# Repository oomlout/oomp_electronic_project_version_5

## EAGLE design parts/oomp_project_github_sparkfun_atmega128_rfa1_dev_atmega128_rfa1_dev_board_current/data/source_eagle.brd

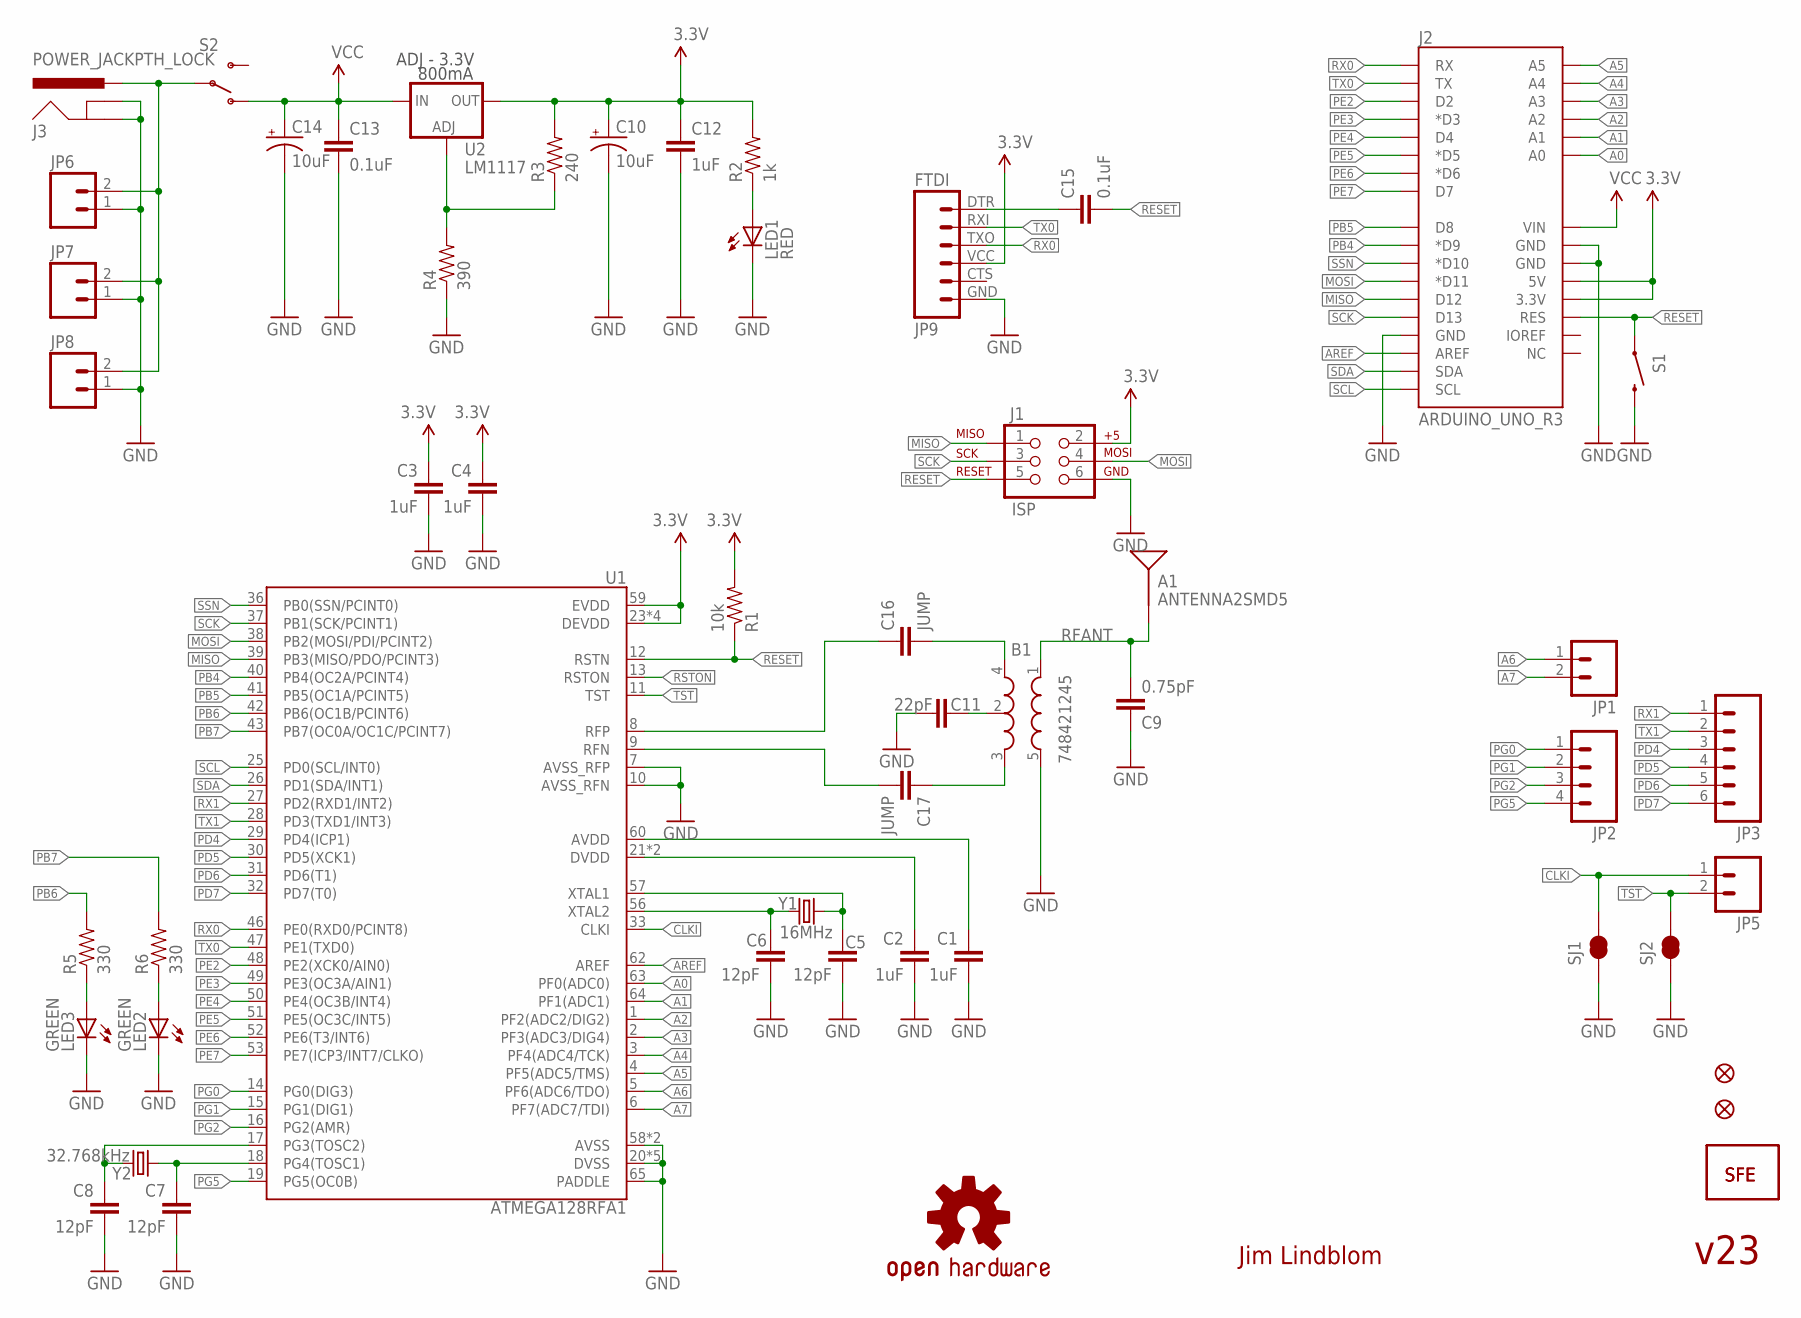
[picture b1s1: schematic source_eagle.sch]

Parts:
A1: ANTENNA2SMD5; ANTENNA-CHIP5
B1: 748421245; BALUN
C1, C2, C3, C4, C12: 1uF; 0402-CAP
C5, C6, C7, C8: 12pF; 0402-CAP
C9: 0.75pF; 0402-CAP
C10, C14: 10uF; EIA3216
C11: 22pF; 0402-CAP
C13, C15: 0.1uF; 0402-CAP
C16, C17: JUMP; 0402-CAP
FID1, FID2: FIDUCIALUFIDUCIAL; MICRO-FIDUCIAL
J1: ISP; 2X3-NS
J2: ARDUINO_UNO_R3
J3: POWER_JACKPTH_LOCK; POWER_JACK_PTH_LOCK
JP1, JP5, JP7: M021X02_NO_SILK; 1X02_NO_SILK
JP2: M041X04_NO_SILK; 1X04_NO_SILK
JP3: M06SIP-NS; 1X06_NS
JP4, JP10: LOGO-SFENEW; SFE-NEW-WEBLOGO
JP6: M02JST-PTH-2; JST-2-PTH
JP8: M023.5MM-NO_SILK; SCREWTERMINAL-3.5MM-2-NS
JP9: FTDI; FTDI_BASIC
LED1: RED; LED-0603
LED2, LED3: GREEN; LED-0603
R1: 10k; 0402-RES
R2: 1k; 0402-RES
R3: 240; 0402-RES
R4: 390; 0402-RES
R5, R6: 330; 0402-RES
S1: SWITCH-MOMENTARY-2SMD; TACTILE_SWITCH_SMD
S2: SWITCH-SPST-SMD-A
SJ1, SJ2: SOLDERJUMPERTRACE; SJ_2S-TRACE
U1: ATMEGA128RFA1; QFN-64
U2: LM1117; SOT223
U$1: OSHW-LOGOS; OSHW-LOGO-S
Y1: 16MHz; CRYSTAL-SMD-5X3
Y2: 32.768kHz; CRYSTAL-32KHZ-SMD

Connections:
3.3V: C3.1, C4.1, C10.A (+), C12.1, J1.2, J2.3.3V, J2.5V, JP9.VCC (4), R1.2, R2.2, R3.2, U1.23 (DEVDD), U1.34 (DEVDD), U1.44 (DEVDD), U1.54 (DEVDD), U1.59 (EVDD), U2.2 (OUT)
A0: J2.A0, U1.63 (PF0(ADC0))
A1: J2.A1, U1.64 (PF1(ADC1))
A2: J2.A2, U1.1 (PF2(ADC2/DIG2))
A3: J2.A3, U1.2 (PF3(ADC3/DIG4))
A4: J2.A4, U1.3 (PF4(ADC4/TCK))
A5: J2.A5, U1.4 (PF5(ADC5/TMS))
A6: JP1.1, U1.5 (PF6(ADC6/TDO))
A7: JP1.2, U1.6 (PF7(ADC7/TDI))
AREF: J2.AREF, U1.62 (AREF)
AVDD: C1.1, U1.60 (AVDD)
CLKI: JP5.1, SJ1.2, U1.33 (CLKI)
DTR: C15.1, JP9.DTR (1)
DVDD: C2.1, U1.21 (DVDD), U1.22 (DVDD)
FB: R3.1, R4.2, U2.1 (ADJ)
GND: B1.5 (GND), C1.2, C2.2, C3.2, C4.2, C5.2, C6.2, C7.2, C8.2, C9.1, C10.C (-), C11.2, C12.2, C13.2, C14.C (-), J1.6, J2.GND@0 (GND), J2.GND@1 (GND), J2.GND@2 (GND), J3.GND, J3.GNDBREAK, JP6.1, JP7.1, JP8.1, JP9.GND (6), LED1.C, LED2.C, LED3.C, R4.1, S1.3 (2), SJ1.1, SJ2.1, U1.7 (AVSS_RFP), U1.10 (AVSS_RFN), U1.20 (DVSS), U1.24 (DVSS), U1.35 (DVSS), U1.45 (DVSS), U1.55 (DVSS), U1.58 (AVSS), U1.61 (AVSS), U1.65 (PADDLE)
MISO: J1.1, J2.D12, U1.39 (PB3(MISO/PDO/PCINT3))
MOSI: J1.4, J2.D11 (*D11), U1.38 (PB2(MOSI/PDI/PCINT2))
unnamed: LED1.A, R2.1
unnamed: C5.1, U1.57 (XTAL1), Y1.3 (2)
unnamed: C6.1, U1.56 (XTAL2), Y1.1
unnamed: C7.1, U1.18 (PG4(TOSC1)), Y2.X1 (1)
unnamed: C8.1, U1.17 (PG3(TOSC2)), Y2.X2 (2)
unnamed: B1.2 (GND), C11.1
unnamed: LED3.A, R5.1
unnamed: J3.PWR, JP6.2, JP7.2, JP8.2, S2.2
unnamed: B1.4 (OUT1), C16.2
unnamed: B1.3 (OUT2), C17.1
unnamed: LED2.A, R6.1
PB4: J2.D9 (*D9), U1.40 (PB4(OC2A/PCINT4))
PB5: J2.D8, U1.41 (PB5(OC1A/PCINT5))
PB6: R5.2, U1.42 (PB6(OC1B/PCINT6))
PB7: R6.2, U1.43 (PB7(OC0A/OC1C/PCINT7))
PD4: JP3.3, U1.29 (PD4(ICP1))
PD5: JP3.4, U1.30 (PD5(XCK1))
PD6: JP3.5, U1.31 (PD6(T1))
PD7: JP3.6, U1.32 (PD7(T0))
PE2: J2.D2, U1.48 (PE2(XCK0/AIN0))
PE3: J2.D3 (*D3), U1.49 (PE3(OC3A/AIN1))
PE4: J2.D4, U1.50 (PE4(OC3B/INT4))
PE5: J2.D5 (*D5), U1.51 (PE5(OC3C/INT5))
PE6: J2.D6 (*D6), U1.52 (PE6(T3/INT6))
PE7: J2.D7, U1.53 (PE7(ICP3/INT7/CLKO))
PG0: JP2.1, U1.14 (PG0(DIG3))
PG1: JP2.2, U1.15 (PG1(DIG1))
PG2: JP2.3, U1.16 (PG2(AMR))
PG5: JP2.4, U1.19 (PG5(OC0B))
RESET: C15.2, J1.5, J2.RES, R1.1, S1.1, U1.12 (RSTN)
RFANT: A1.FEED, B1.1 (IN), C9.2
RFN: C17.2, U1.9 (RFN)
RFP: C16.1, U1.8 (RFP)
RSTON: U1.13 (RSTON)
RX0: J2.RX, JP9.TXO (3), U1.46 (PE0(RXD0/PCINT8))
RX1: JP3.1, U1.27 (PD2(RXD1/INT2))
SCK: J1.3, J2.D13, U1.37 (PB1(SCK/PCINT1))
SCL: J2.SCL, U1.25 (PD0(SCL/INT0))
SDA: J2.SDA, U1.26 (PD1(SDA/INT1))
SSN: J2.D10 (*D10), U1.36 (PB0(SSN/PCINT0))
TST: JP5.2, SJ2.2, U1.11 (TST)
TX0: J2.TX, JP9.RXI (2), U1.47 (PE1(TXD0))
TX1: JP3.2, U1.28 (PD3(TXD1/INT3))
VCC: C13.1, C14.A (+), J2.VIN, S2.1 (O), U2.3 (IN)

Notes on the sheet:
Jim Lindblom
800mA
ADJ - 3.3V
v23

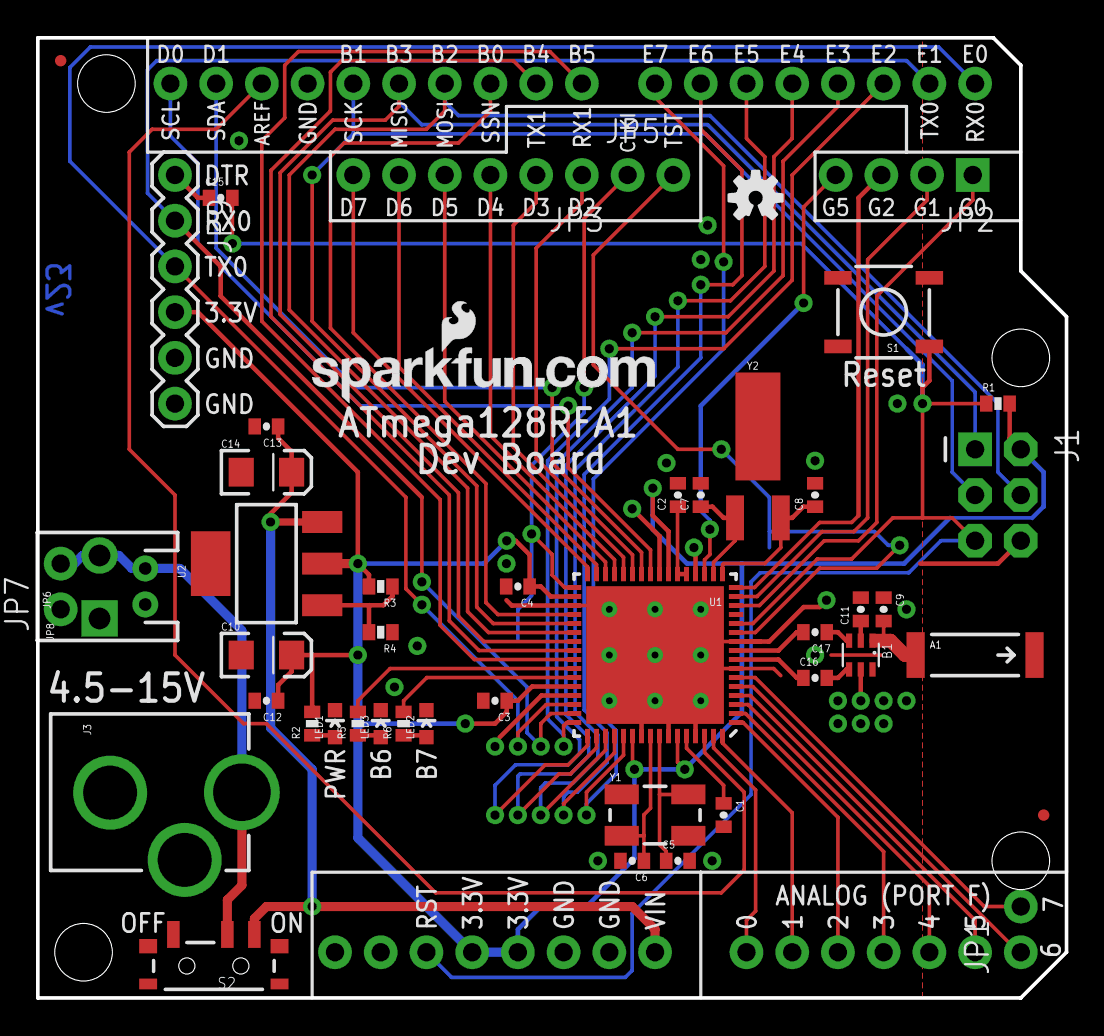
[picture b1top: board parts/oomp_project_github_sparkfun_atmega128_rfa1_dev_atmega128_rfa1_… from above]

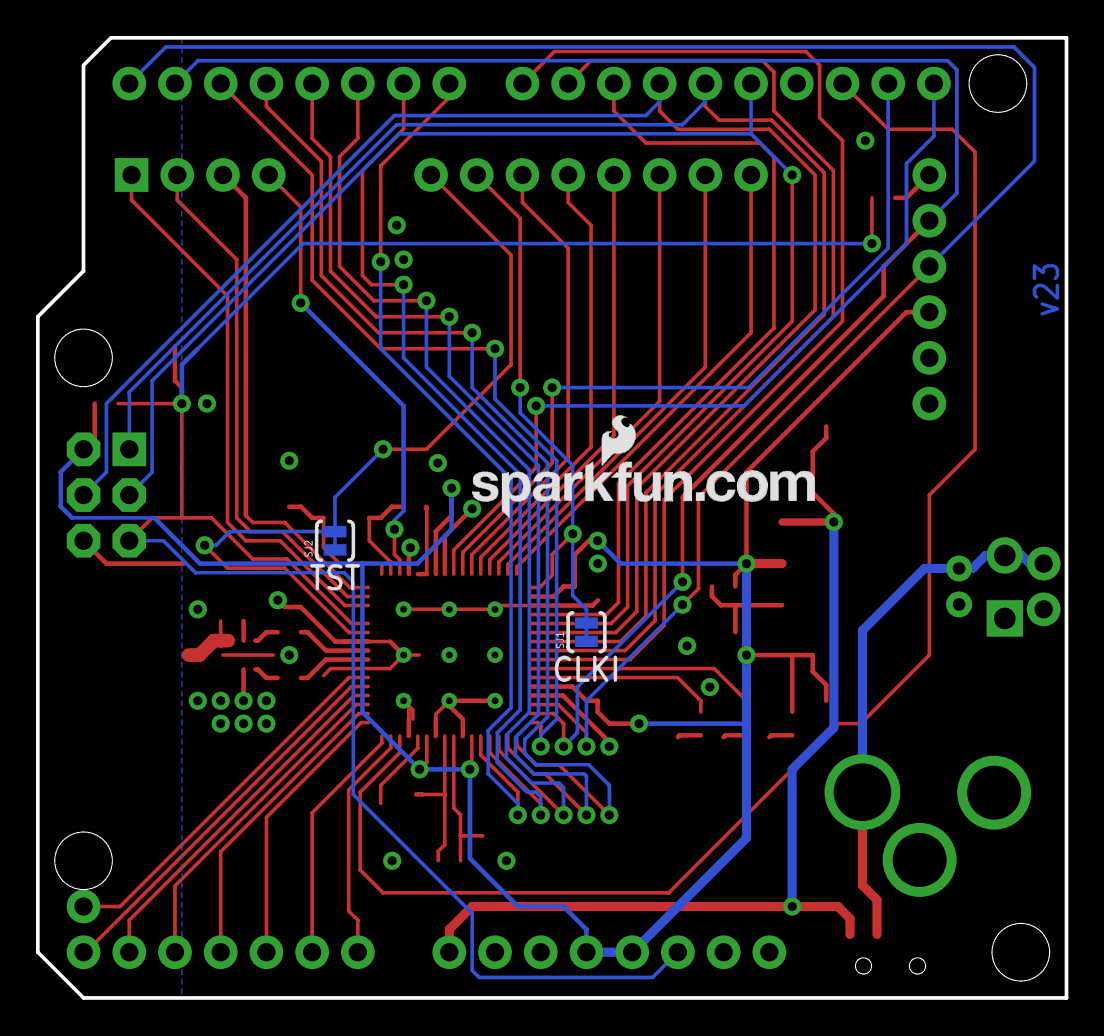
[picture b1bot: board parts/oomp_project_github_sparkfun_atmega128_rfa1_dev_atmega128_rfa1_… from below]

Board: 2 copper layers, 57.1 x 53.3 mm, 52 parts (3 on the bottom side), 61 nets.

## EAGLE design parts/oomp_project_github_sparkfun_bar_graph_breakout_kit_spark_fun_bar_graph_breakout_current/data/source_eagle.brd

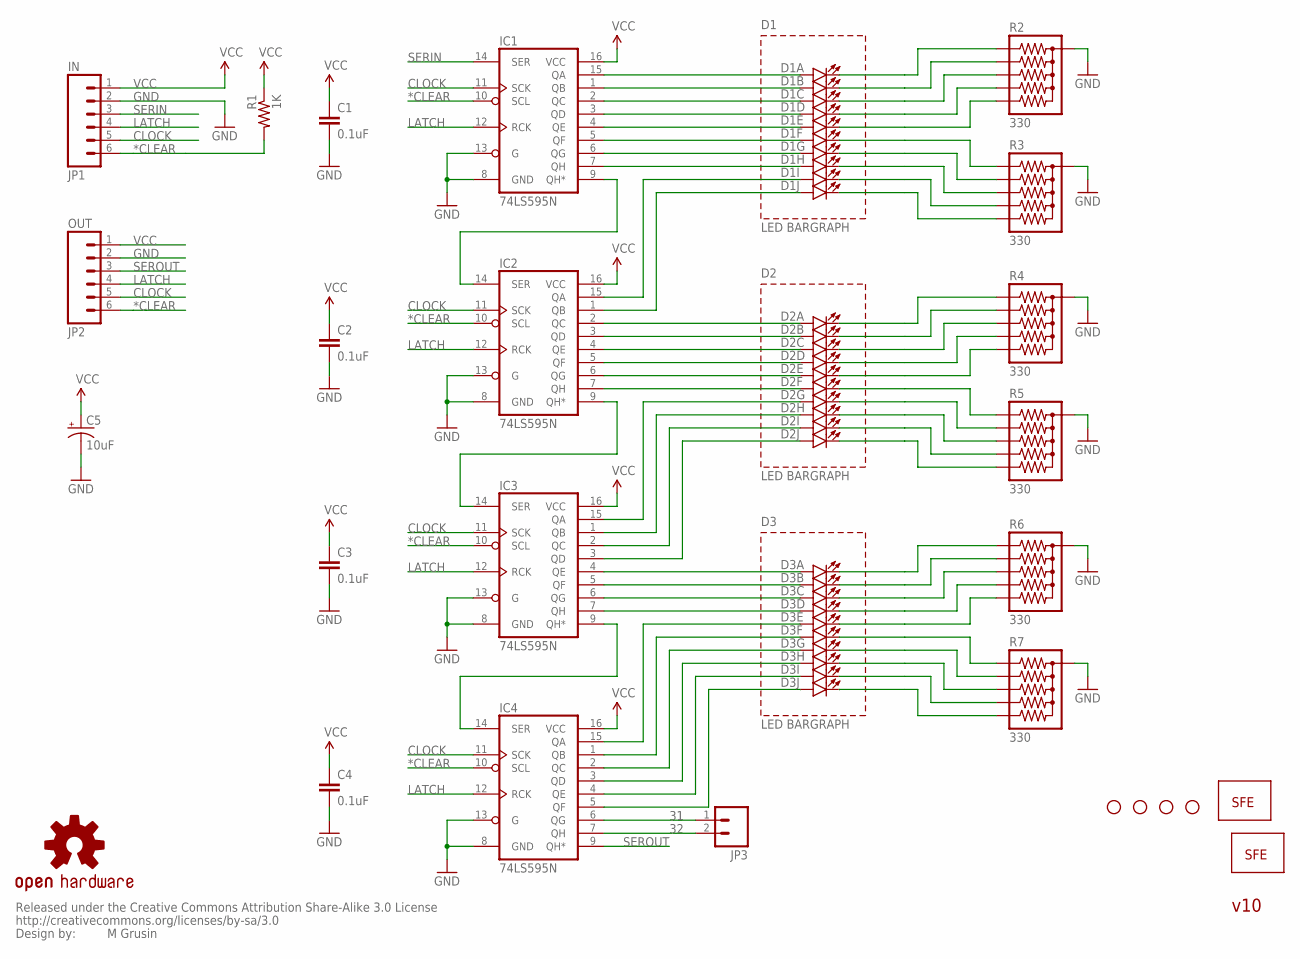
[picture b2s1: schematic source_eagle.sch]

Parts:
C1, C2, C3, C4: 0.1uF; CAP-PTH-SMALL2
C5: 10uF; CPOL-RADIAL-10UF-25V
D1, D2, D3: LED_BARGRAPH_10; LED_BARGAPH_10
IC1, IC2, IC3, IC4: 74LS595N; DIL16
JP1: IN; 1X06
JP2: OUT; 1X06
JP3: M02PTH; 1X02
LOGO1: LOGO-SFENW2; SFE-NEW-WEB
LOGO2: LOGO-SFESK; SFE-LOGO-FLAME
R1: 1K; AXIAL-0.3
R2, R3, R4, R5, R6, R7: 330; RPACK-SIP-PTH-5
SO1, SO2, SO3, SO4: STAND-OFF
U$5: OSHW-LOGOM; OSHW-LOGO-M
U$6: CREATIVE_COMMONS

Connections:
31: IC4.6 (QG), JP3.1
32: IC4.7 (QH), JP3.2
*CLEAR: IC1.10 (SCL), IC2.10 (SCL), IC3.10 (SCL), IC4.10 (SCL), JP1.6, JP2.6, R1.P$2 (2)
CLOCK: IC1.11 (SCK), IC2.11 (SCK), IC3.11 (SCK), IC4.11 (SCK), JP1.5, JP2.5
GND: C1.2, C2.2, C3.2, C4.2, C5.2 (-), IC1.8 (GND), IC1.13 (G), IC2.8 (GND), IC2.13 (G), IC3.8 (GND), IC3.13 (G), IC4.8 (GND), IC4.13 (G), JP1.2, JP2.2, R2.P$1 (1), R3.P$1 (1), R4.P$1 (1), R5.P$1 (1), R6.P$1 (1), R7.P$1 (1)
LATCH: IC1.12 (RCK), IC2.12 (RCK), IC3.12 (RCK), IC4.12 (RCK), JP1.4, JP2.4
unnamed: D1.1 (A), IC1.15 (QA)
unnamed: D1.2 (A), IC1.1 (QB)
unnamed: D1.3 (A), IC1.2 (QC)
unnamed: D1.4 (A), IC1.3 (QD)
unnamed: D1.5 (A), IC1.4 (QE)
unnamed: D1.6 (A), IC1.5 (QF)
unnamed: D1.7 (A), IC1.6 (QG)
unnamed: D1.8 (A), IC1.7 (QH)
unnamed: D1.9 (A), IC2.15 (QA)
unnamed: D1.10 (A), IC2.1 (QB)
unnamed: D2.8 (A), IC3.1 (QB)
unnamed: D2.7 (A), IC3.15 (QA)
unnamed: D2.9 (A), IC3.2 (QC)
unnamed: D2.10 (A), IC3.3 (QD)
unnamed: D3.1 (A), IC3.4 (QE)
unnamed: D3.2 (A), IC3.5 (QF)
unnamed: D3.3 (A), IC3.6 (QG)
unnamed: D3.4 (A), IC3.7 (QH)
unnamed: D2.1 (A), IC2.2 (QC)
unnamed: D2.2 (A), IC2.3 (QD)
unnamed: D2.3 (A), IC2.4 (QE)
unnamed: D2.4 (A), IC2.5 (QF)
unnamed: D2.5 (A), IC2.6 (QG)
unnamed: D2.6 (A), IC2.7 (QH)
unnamed: D1.20 (C), R2.P$2 (2)
unnamed: D1.19 (C), R2.P$3 (3)
unnamed: D3.5 (A), IC4.15 (QA)
unnamed: D3.6 (A), IC4.1 (QB)
unnamed: D1.18 (C), R2.P$4 (4)
unnamed: D1.17 (C), R2.P$5 (5)
unnamed: D1.16 (C), R2.P$6 (6)
unnamed: D1.15 (C), R3.P$2 (2)
unnamed: D1.14 (C), R3.P$3 (3)
unnamed: D1.13 (C), R3.P$4 (4)
unnamed: D1.12 (C), R3.P$5 (5)
unnamed: D1.11 (C), R3.P$6 (6)
unnamed: D2.20 (C), R4.P$2 (2)
unnamed: D2.19 (C), R4.P$3 (3)
unnamed: D3.7 (A), IC4.2 (QC)
unnamed: D3.8 (A), IC4.3 (QD)
unnamed: D3.9 (A), IC4.4 (QE)
unnamed: D3.10 (A), IC4.5 (QF)
unnamed: D2.18 (C), R4.P$4 (4)
unnamed: D2.17 (C), R4.P$5 (5)
unnamed: D2.16 (C), R4.P$6 (6)
unnamed: D2.15 (C), R5.P$2 (2)
unnamed: D2.14 (C), R5.P$3 (3)
unnamed: D2.13 (C), R5.P$4 (4)
unnamed: D2.12 (C), R5.P$5 (5)
unnamed: D2.11 (C), R5.P$6 (6)
unnamed: D3.20 (C), R6.P$2 (2)
unnamed: D3.19 (C), R6.P$3 (3)
unnamed: D3.18 (C), R6.P$4 (4)
unnamed: D3.17 (C), R6.P$5 (5)
unnamed: D3.16 (C), R6.P$6 (6)
unnamed: D3.15 (C), R7.P$2 (2)
unnamed: D3.14 (C), R7.P$3 (3)
unnamed: D3.13 (C), R7.P$4 (4)
unnamed: D3.12 (C), R7.P$5 (5)
unnamed: D3.11 (C), R7.P$6 (6)
unnamed: IC1.9 (QH*), IC2.14 (SER)
unnamed: IC2.9 (QH*), IC3.14 (SER)
unnamed: IC3.9 (QH*), IC4.14 (SER)
SERIN: IC1.14 (SER), JP1.3
SEROUT: IC4.9 (QH*), JP2.3
VCC: C1.1, C2.1, C3.1, C4.1, C5.1 (+), IC1.16 (VCC), IC2.16 (VCC), IC3.16 (VCC), IC4.16 (VCC), JP1.1, JP2.1, R1.P$1 (1)

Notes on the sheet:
M Grusin
LED BARGRAPH
v10

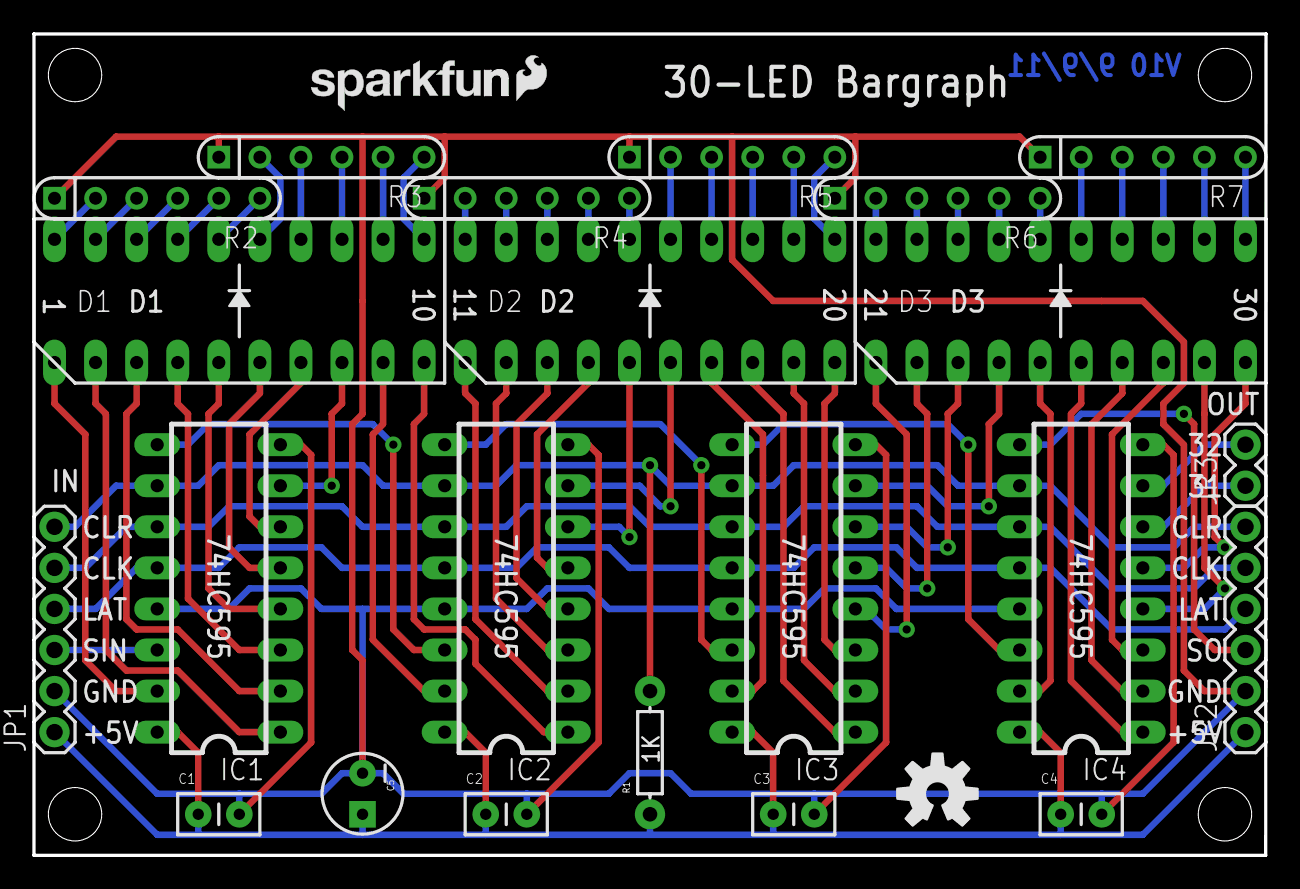
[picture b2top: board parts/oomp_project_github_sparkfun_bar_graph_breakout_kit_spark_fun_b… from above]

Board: 2 copper layers, 76.2 x 50.8 mm, 30 parts (0 on the bottom side), 72 nets.

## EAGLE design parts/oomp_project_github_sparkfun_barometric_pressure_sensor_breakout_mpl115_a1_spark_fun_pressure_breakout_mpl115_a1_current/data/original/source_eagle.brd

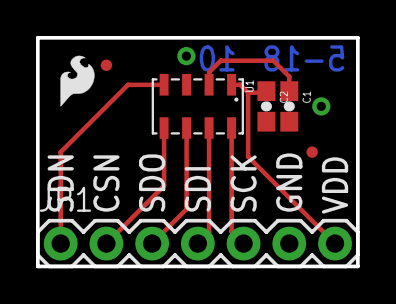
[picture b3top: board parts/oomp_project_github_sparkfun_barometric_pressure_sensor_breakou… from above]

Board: 2 copper layers, 17.8 x 12.7 mm, 8 parts (1 on the bottom side), 8 nets.

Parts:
C1, C2: 1uF; 0603-CAP
FID1, FID2: FIDUCIALUFIDUCIAL; MICRO-FIDUCIAL
JP1: 1X07
JP2: LOGO-SFESK; SFE-LOGO-FLAME
JP3: LOGO-SFENW2; SFE-NEW-WEB
U1: MPL115A; LGA8

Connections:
CAP: C1.1, U1.2
CSN: JP1.2, U1.5
DIN: JP1.4, U1.7
DOUT: JP1.3, U1.6
GND: C1.2, C2.2, JP1.6, U1.3
SCLK: JP1.5, U1.8
SHDN: JP1.1, U1.4
VDD: C2.1, JP1.7, U1.1

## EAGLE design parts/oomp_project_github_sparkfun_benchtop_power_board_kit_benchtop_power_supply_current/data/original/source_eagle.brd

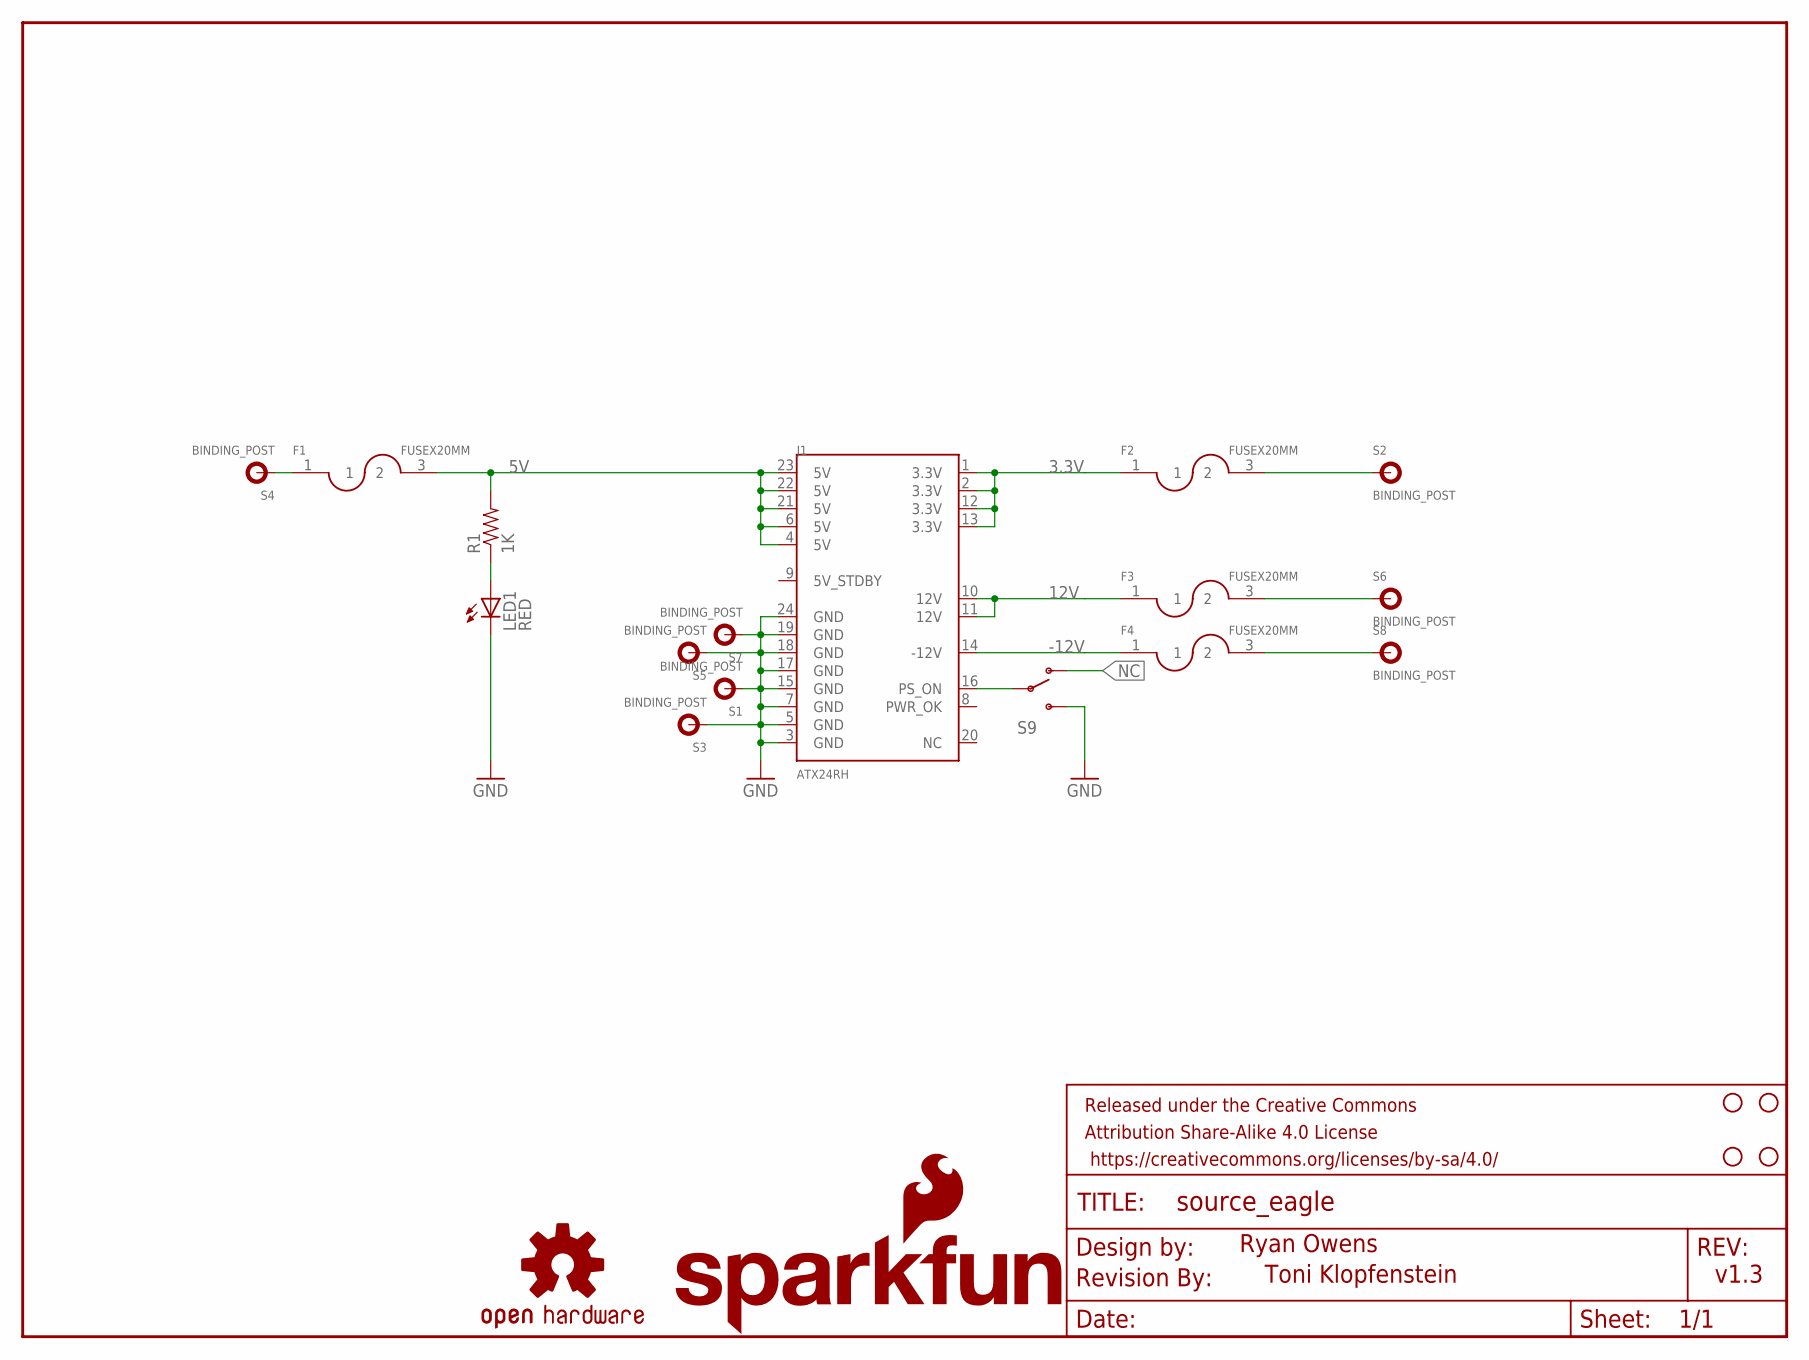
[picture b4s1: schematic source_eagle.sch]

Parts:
F1, F2, F3, F4: FUSEX20MM; FUSE_5MM
FRAME1: FRAME-LETTER; CREATIVE_COMMONS
J1: ATX24RH; ATX24_RIGHT_ANGLE
JP1: SFE_LOGO_NAME_FLAME.3_INCH; SFE_LOGO_NAME_FLAME_.3
JP2, JP3, JP4, JP5: STAND-OFF
LED1: RED; LED5MM
LOGO1: OSHW-LOGOL; OSHW-LOGO-L
R1: 1K; AXIAL-0.3
S1, S2, S3, S4, S5, S6, S7, S8: BINDING_POST
S9: SWITCH-SPDTKIT; SWITCH-SPDT_KIT
U$1: REVISION

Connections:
3.3V: F2.1, J1.1 (3.3V), J1.2 (3.3V), J1.12 (3.3V), J1.13 (3.3V)
3.3V_P: F2.3 (2), S2.P$1
5V: F1.3 (2), J1.4 (5V), J1.6 (5V), J1.21 (5V), J1.22 (5V), J1.23 (5V), R1.P$2 (2)
5V_P: F1.1, S4.P$1
12V: F3.1, J1.10 (12V), J1.11 (12V)
12V_P: F3.3 (2), S6.P$1
-12V: F4.1, J1.14 (-12V)
-12V_P: F4.3 (2), S8.P$1
GND: J1.3 (GND), J1.5 (GND), J1.7 (GND), J1.15 (GND), J1.17 (GND), J1.18 (GND), J1.19 (GND), J1.24 (GND), LED1.K (C), S1.P$1, S3.P$1, S5.P$1, S7.P$1, S9.3 (S)
unnamed: LED1.A, R1.P$1 (1)
unnamed: J1.16 (PS_ON), S9.2
NC: S9.1 (O)

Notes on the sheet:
Ryan Owens
Toni Klopfenstein
v1.3

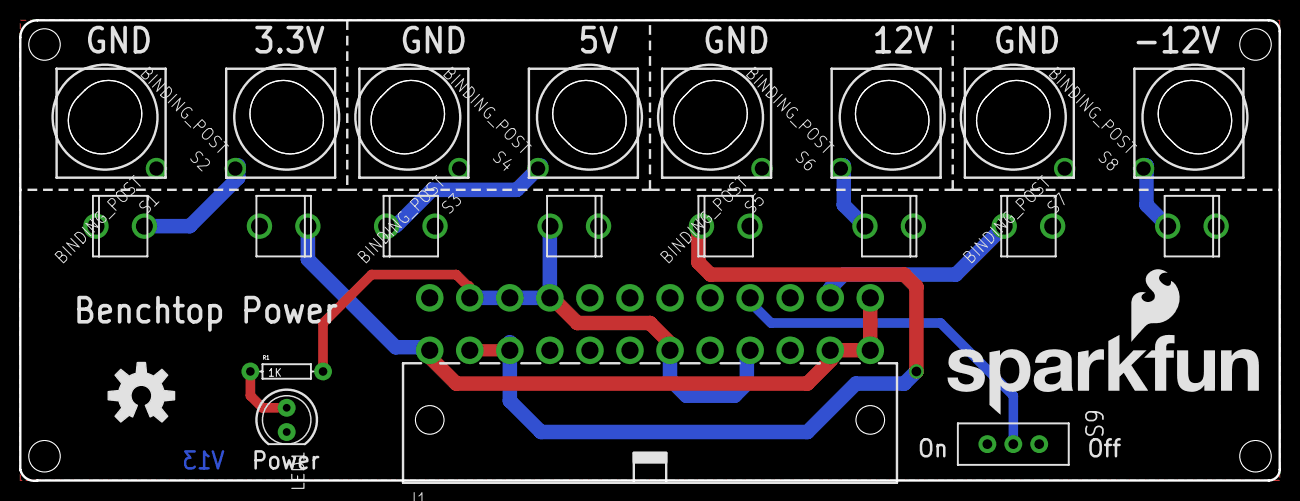
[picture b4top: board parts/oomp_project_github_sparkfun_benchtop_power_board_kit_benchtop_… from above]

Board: 2 copper layers, 132.1 x 48.3 mm, 24 parts (0 on the bottom side), 11 nets.

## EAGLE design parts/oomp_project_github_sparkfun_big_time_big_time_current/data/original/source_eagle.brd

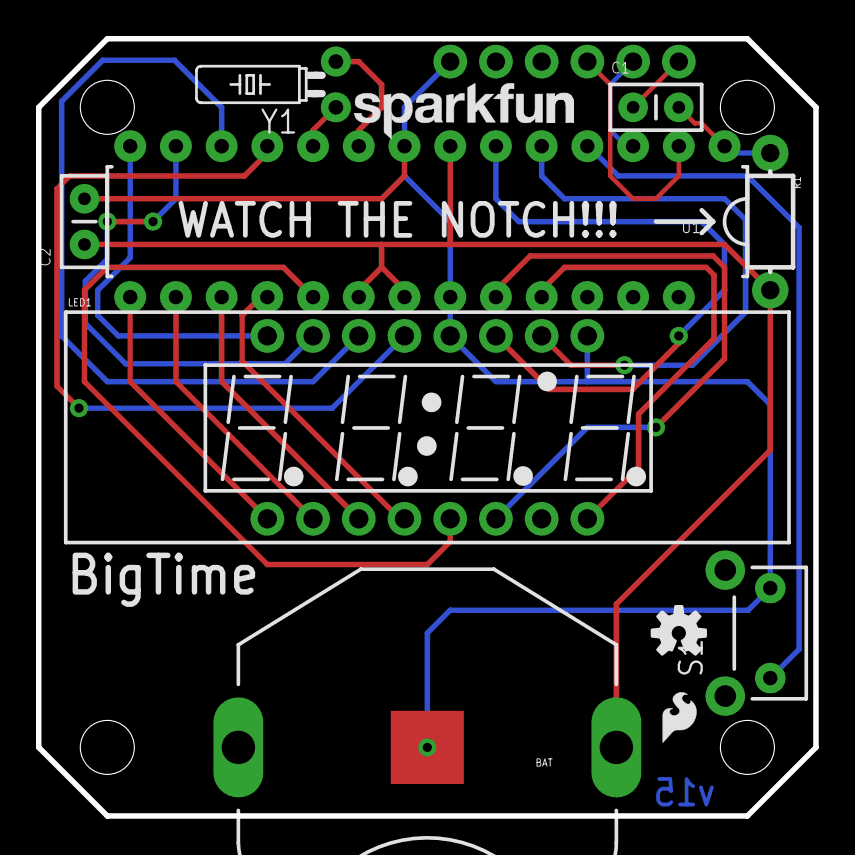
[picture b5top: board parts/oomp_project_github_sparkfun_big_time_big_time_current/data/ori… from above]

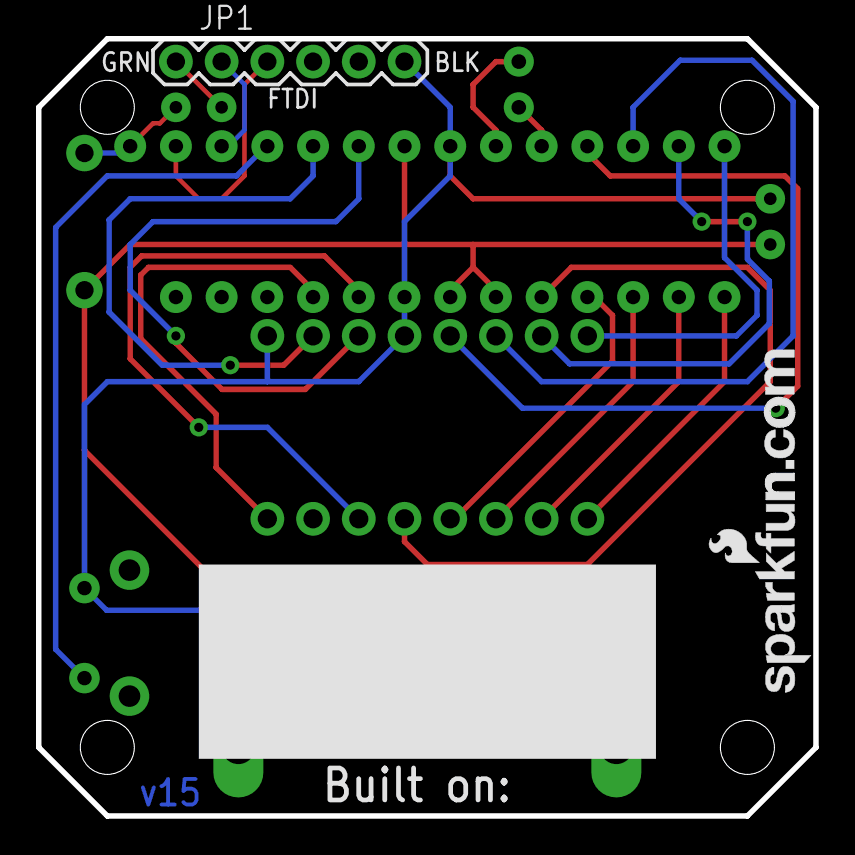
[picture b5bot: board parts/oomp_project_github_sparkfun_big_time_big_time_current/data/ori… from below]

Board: 2 copper layers, 43.2 x 43.2 mm, 14 parts (2 on the bottom side), 22 nets.

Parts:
BAT: BATTERY_20MM_PTH_COMPACT
C1, C2: 100nF; CAP-PTH-SMALLEZ
JP1: FTDI_BASICPTH; FTDI_BASIC
LED1: 7-SEGMENT-4DIGIT-YOUNGSUNKIT; 7-SEGMENT-4DIGIT-YOUNGSUN-KIT
R1: 100k; AXIAL-0.3-KIT
S1: BUTTON; TACTILE-PTH-SIDEEZ
U1: ATMEGA328P_PDIP_EZ; DIL28-EZ
U$1: LOGO-SFESK; SFE-LOGO-FLAME
U$2: CREATIVE_COMMONS
U$3: LOGO-SFENEW; SFE-NEW-WEBLOGO
U$4: OSHW-LOGOS; OSHW-LOGO-S
U$5: LOGO-SFENW2; SFE-NEW-WEB
Y1: 32.768kHz; TC26HEZ

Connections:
A: LED1.14, U1.12
AMPM: LED1.10, U1.5
B: LED1.16, U1.14
BTN: S1.1, U1.4
C: LED1.13, U1.11
COL: LED1.4, U1.18
D: LED1.3, U1.17
DIG1: LED1.1, U1.15
DIG2: LED1.2, U1.16
DIG3: LED1.6, U1.23
DIG4: LED1.8, U1.24
E: LED1.5, U1.19
F: LED1.11, U1.6
G: LED1.15, U1.13
GND: BAT.2, C2.2, JP1.GND, LED1.9, LED1.12, S1.2, U1.8, U1.22
unnamed: U1.10, Y1.1
unnamed: U1.9, Y1.2
unnamed: C1.1, JP1.DTR
RST: C1.2, R1.P$1, U1.1
RXI: JP1.TXO, U1.2
TXO: JP1.RXI, U1.3
VCC: BAT.1, C2.1, R1.P$2, U1.7, U1.20, U1.21

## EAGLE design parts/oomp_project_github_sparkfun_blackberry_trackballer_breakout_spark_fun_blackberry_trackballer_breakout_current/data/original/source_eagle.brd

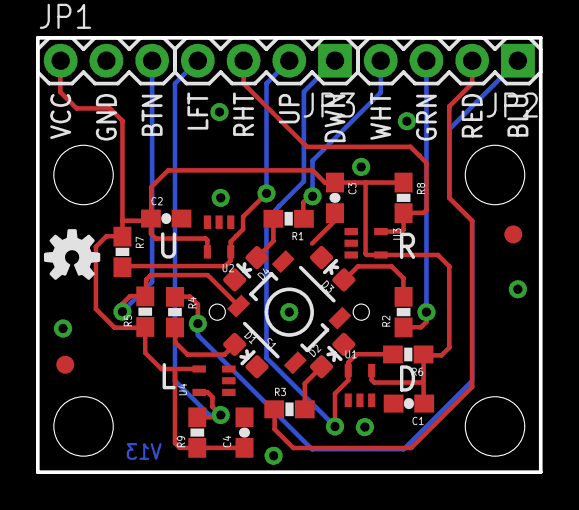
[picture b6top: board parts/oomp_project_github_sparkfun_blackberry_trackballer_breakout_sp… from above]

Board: 2 copper layers, 27.9 x 24.1 mm, 35 parts (1 on the bottom side), 15 nets.

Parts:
C1, C2, C3, C4: 0.1uF; 0603-CAP
D1: BLU; LED-0603
D2: RED; LED-0603
D3: GRN; LED-0603
D4: WHT; LED-0603
E$1, E$2: FIDUCIAL1X2; FIDUCIAL-1X2
FRAME1: FRAME-LETTER; CREATIVE_COMMONS
JP1: 1X03
JP2, JP3: 1X04
LOGO1: SFE_LOGO_NAME_FLAME.2_INCH; SFE_LOGO_NAME_FLAME_.2
LOGO2: OSHW-LOGOS; OSHW-LOGO-S
R1, R2, R3, R4: 180; 0603-RES
R5, R6, R7, R8, R9: 10K; 0603-RES
S1: SWITCH-MOMENTARY-2SMD-2; TACTILE_SWITCH_SMD-2
U1, U2, U3, U4: HALL-EFFECTSMD; SC70
U$1, U$8, U$11, U$14: STAND-OFF
U$3: TRACKBALLMECH; TRACKBALL

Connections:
BLU: JP2.1, R4.1
BTN: JP1.3, R5.2, S1.1
DWN: JP3.2, R7.2, U2.5
GND: C1.2, C2.2, C3.2, C4.2, D1.C, D2.C, D3.C, D4.C, JP1.2, S1.2, U1.2, U2.2, U3.2, U4.2
GRN: JP2.3, R2.1
LFT: JP3.3, R8.2, U3.5
unnamed: D3.A, R2.2
unnamed: D2.A, R3.2
unnamed: D1.A, R4.2
unnamed: D4.A, R1.2
RED: JP2.2, R3.1
RHT: JP3.4, R9.2, U4.5
UP: JP3.1, R6.2, U1.5
VCC: C1.1, C2.1, C3.1, C4.1, JP1.1, R5.1, R6.1, R7.1, R8.1, R9.1, U1.4, U2.4, U3.4, U4.4
WHT: JP2.4, R1.1

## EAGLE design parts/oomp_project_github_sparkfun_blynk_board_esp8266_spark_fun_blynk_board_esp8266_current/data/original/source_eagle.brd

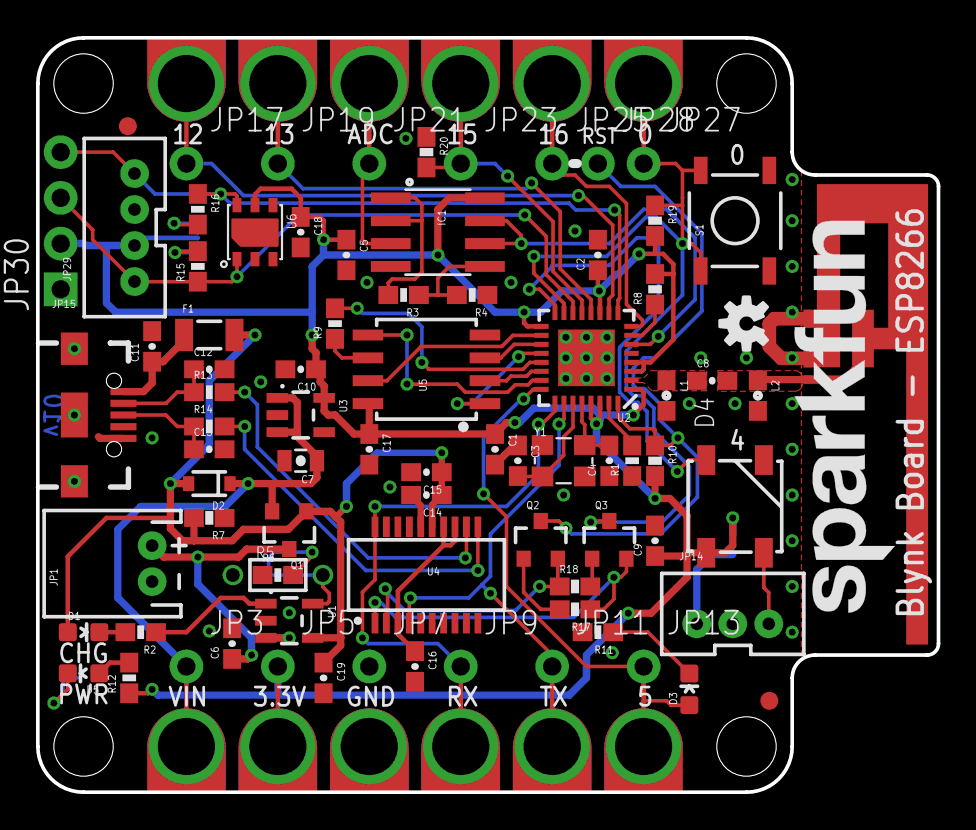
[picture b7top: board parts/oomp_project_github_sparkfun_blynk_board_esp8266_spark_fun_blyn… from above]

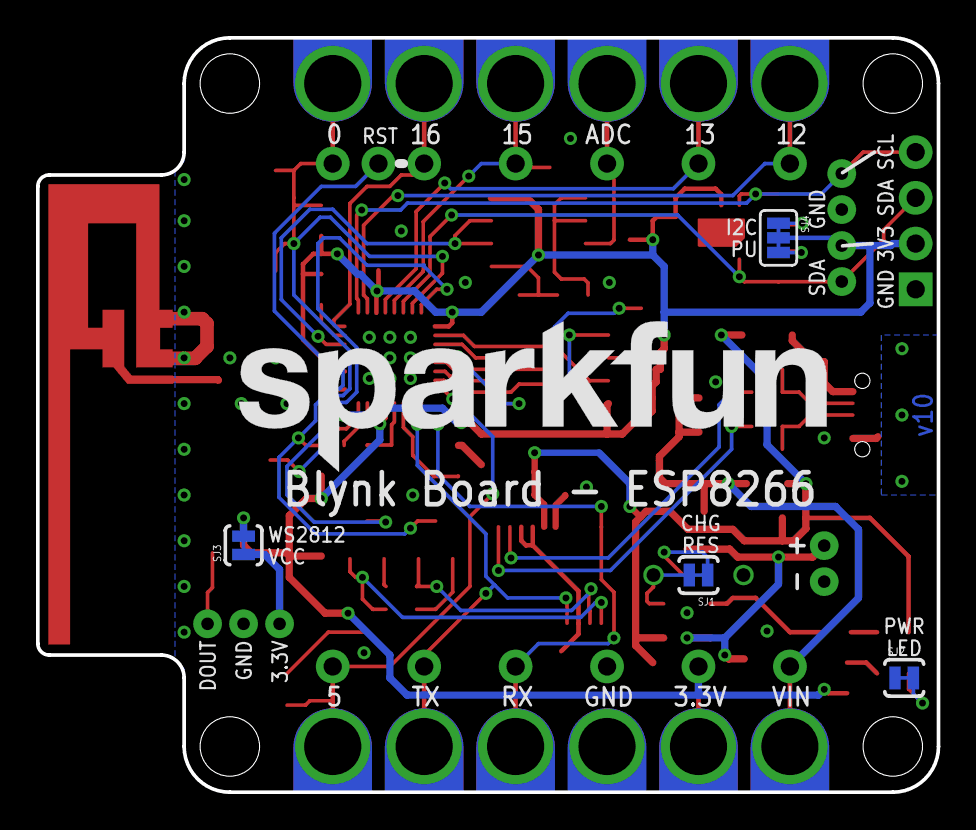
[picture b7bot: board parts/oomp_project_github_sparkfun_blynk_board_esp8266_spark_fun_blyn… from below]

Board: 2 copper layers, 50.0 x 41.9 mm, 104 parts (5 on the bottom side), 56 nets.

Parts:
C1: 10uF; 0603-CAP
C2, C5, C9, C11, C14, C16, C17, C18: 0.1uF; 0603-CAP
C3, C4: 10pF; 0603-CAP
C6, C15, C19: 4.7uF; 0603-CAP
C7: 1.0uF; 0805-CAP
C8: 5.6pF; 0603-CAP
C10: 2.2uF; 0603-CAP
C12, C13: 47pF; 0603-CAP
D1: Yellow; LED-0603
D2: BAT20J; SOD-323
D3: BLUE; LED-0603
D4: WS2812; WS2812B
D5: RED; LED-0603
E1: ANTENNATRACE; TRACE_ANTENNA_2.4GHZ_25.7MM
F1: 500mA; PTC-1206
FID1, FID2: FIDUCIAL1X2; FIDUCIAL-1X2
FRAME1: FRAME-LEDGER; CREATIVE_COMMONS
IC1: LMV358; SO08
JP1: JST_2; JST-2-PTH
JP2, JP4, JP6, JP8, JP10, JP12, JP16, JP18, JP20, JP22, JP24, JP26: DNP; 1X01_ALLIGATOR_3MM_HALF
JP3, JP5, JP7, JP9, JP11, JP13, JP17, JP19, JP21, JP23, JP25, JP27, JP28: DNP; 1X01_NO_SILK
JP14: JST-3; JST-3-PTH-VERT
JP15: USB; USB-B-MICRO-SMD_V03
JP29: JST-4; JST-4-PTH-VERT
JP30: DNP; 1X04_NO_SILK
L1, L2: DNP; 0603
LOGO1: SFE_LOGO_NAME.2_INCH; SFE_LOGO_NAME_.2
LOGO2: OSHW-LOGOS; OSHW-LOGO-S
LOGO3: SFE_LOGO_NAME.3_INCH; SFE_LOGO_NAME_.3
Q1: 2.5A/30V; SOT23-3
Q2, Q3: MMBT2222A; SOT23-3@1
R1: 12k; 0603-RES
R2, R12: 1K; 0603-RES
R3: 22K; 0603-RES
R4: 10K; 0603-RES
R5: DNP; 1/6W-RES
R6: 2.0k; 0603-RES
R7, R8, R10, R17, R18, R19, R20: 10K; 0603-RES@1
R9: 200; 0603-RES
R11: 330; 0603-RES
R13, R14: 27; 0603-RES
R15, R16: 4.7K; 0603-RES
S1: GP0; TACTILE-SWITCH-SMD
SJ1: DNP; PAD-JUMPER-2-NC_BY_TRACE_YES_SILK
SJ2: PWRLED; PAD-JUMPER-2-NC_BY_TRACE_YES_SILK
SJ3: WS2812-VCC; PAD-JUMPER-2-NC_BY_TRACE_YES_SILK
SJ4: DNP; PAD-JUMPER-3-3OF3_NC_BY_TRACE_YES_SILK_FULL_BOX
STANDOFF1, STANDOFF2, STANDOFF3, STANDOFF4: STAND-OFF
U1: MCP73831; SOT23-5
U2: ESP8266; QFN32
U3: AP2112K-3.3V; SOT23-5
U4: FT231XS-U; SSOP20_L
U5: W25Q32FVSS; SOIC-8
U6: SI7021
Y1: 26MHz; CRYSTAL-SMD-3.2X2.5

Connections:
0/BUTTON: JP26.1@2, JP27.1, Q3.3, R19.1, S1.1, S1.2, U2.15
2/SDA: JP29.1, JP30.3, R15.1, U2.14, U6.DATA
3.3V_F: C16.1, U4.3, U4.13, U4.14
4/WS2812: D4.4, U2.16
14/SCL: JP29.4, JP30.4, R16.1, U2.9, U6.SCK
ADC: IC1.6, IC1.7, U2.6
ADC-IN: IC1.3, JP20.1@2, JP21.1
CHIP_EN: R8.1, U2.7
D+: C13.1, JP15.D+, R14.1
D-: C12.1, JP15.D-, R13.1
DTR: Q3.2, R17.1, U4.1
GND: C1.2, C2.2, C3.1, C4.1, C5.2, C6.2, C7.2, C9.2, C10.2, C11.2, C12.2, C13.2, C14.2, C15.2, C16.2, C17.2, C18.2, C19.2, D4.3, E1.GND, E1.GND2, IC1.4, JP1.1, JP6.1@2, JP7.1, JP14.2, JP15.GND, JP29.3, JP30.1, L1.2, L2.2, R1.1, R4.1, R5.1, R6.1, R7.1, R11.2, R20.1, S1.3, S1.4, SJ2.1, U1.2, U2.EP, U3.2, U4.6, U4.16, U5.4, U6.GND, Y1.2, Y1.4
GPIO5: D3.A, JP12.1@2, JP13.1, U2.24
GPIO12: JP16.1@2, JP17.1, U2.10
GPIO13: JP18.1@2, JP19.1, U2.12
GPIO15: JP22.1@2, JP23.1, R20.2, U2.13
GPIO16: JP24.1@2, JP25.1, U2.8
LNA: C8.1, L1.1, U2.2
unnamed: R1.2, U2.31
unnamed: C4.2, U2.28, Y1.3
unnamed: C3.2, U2.27, Y1.1
unnamed: R13.2, U4.12
unnamed: D5.C, SJ2.2
unnamed: Q2.1, R17.2
unnamed: R14.2, U4.11
unnamed: D3.C, R11.1
unnamed: R2.1, U1.1
unnamed: D5.A, R12.2
unnamed: R15.2, SJ4.3
unnamed: Q3.1, R18.2
unnamed: R16.2, SJ4.1
unnamed: R5.2, SJ1.2, U1.5
unnamed: IC1.1, IC1.2, R3.2
unnamed: R6.2, SJ1.1
unnamed: D1.C, R2.2
unnamed: IC1.5, R3.1, R4.2
unnamed: JP14.1, SJ3.1
RESET: JP28.1, Q2.3, R10.1, U2.32
RTS: Q2.2, R18.1, U4.2
SD_!HD!: U2.18, U5.7
SD_!WP!: U2.19, U5.3
SD_CLK: R9.1, U5.6
SD_CLK0: R9.2, U2.21
SD_CS0: U2.20, U5.1
SD_SI: U2.23, U5.5
SD_SO: U2.22, U5.2
SHIELD: JP15.SHIELD1, JP15.SHIELD2, JP15.SHIELD3
TRACE_ANT: C8.2, E1.ANT, L2.1
U0RXI: JP8.1@2, JP9.1, U2.25, U4.20
U0TXO: JP10.1@2, JP11.1, U2.26, U4.4
VCC: C1.1, C2.1, C5.1, C9.1, C10.1, C17.1, C18.1, D4.1, IC1.8, JP4.1@2, JP5.1, JP29.2, JP30.2, R8.2, R10.2, R12.1, R19.2, SJ3.2, SJ4.2, U2.1, U2.3, U2.4, U2.11, U2.17, U2.29, U2.30, U3.5, U5.8, U6.VDD
VIN: C7.1, D2.C, JP2.1@2, JP3.1, Q1.2, U3.1, U3.3
VUSB: C11.1, F1.1, JP15.VBUS
V_BATT: C6.1, JP1.2, Q1.3, U1.3
V_USB: C14.1, C15.1, C19.1, D1.A, D2.A, F1.2, Q1.1, R7.2, U1.4, U4.15
WS2812-DOUT: D4.2, JP14.3

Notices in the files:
parts and their libraries:
SparkFun-Aesthetics: Licensing: CC v3.0 Share-Alike You are welcome to use this library for commercial purposes.
SparkFun-Aesthetics: Released under the Creative Commons
SparkFun-Aesthetics: http://creativecommons.org/licenses/by-sa/3.0
